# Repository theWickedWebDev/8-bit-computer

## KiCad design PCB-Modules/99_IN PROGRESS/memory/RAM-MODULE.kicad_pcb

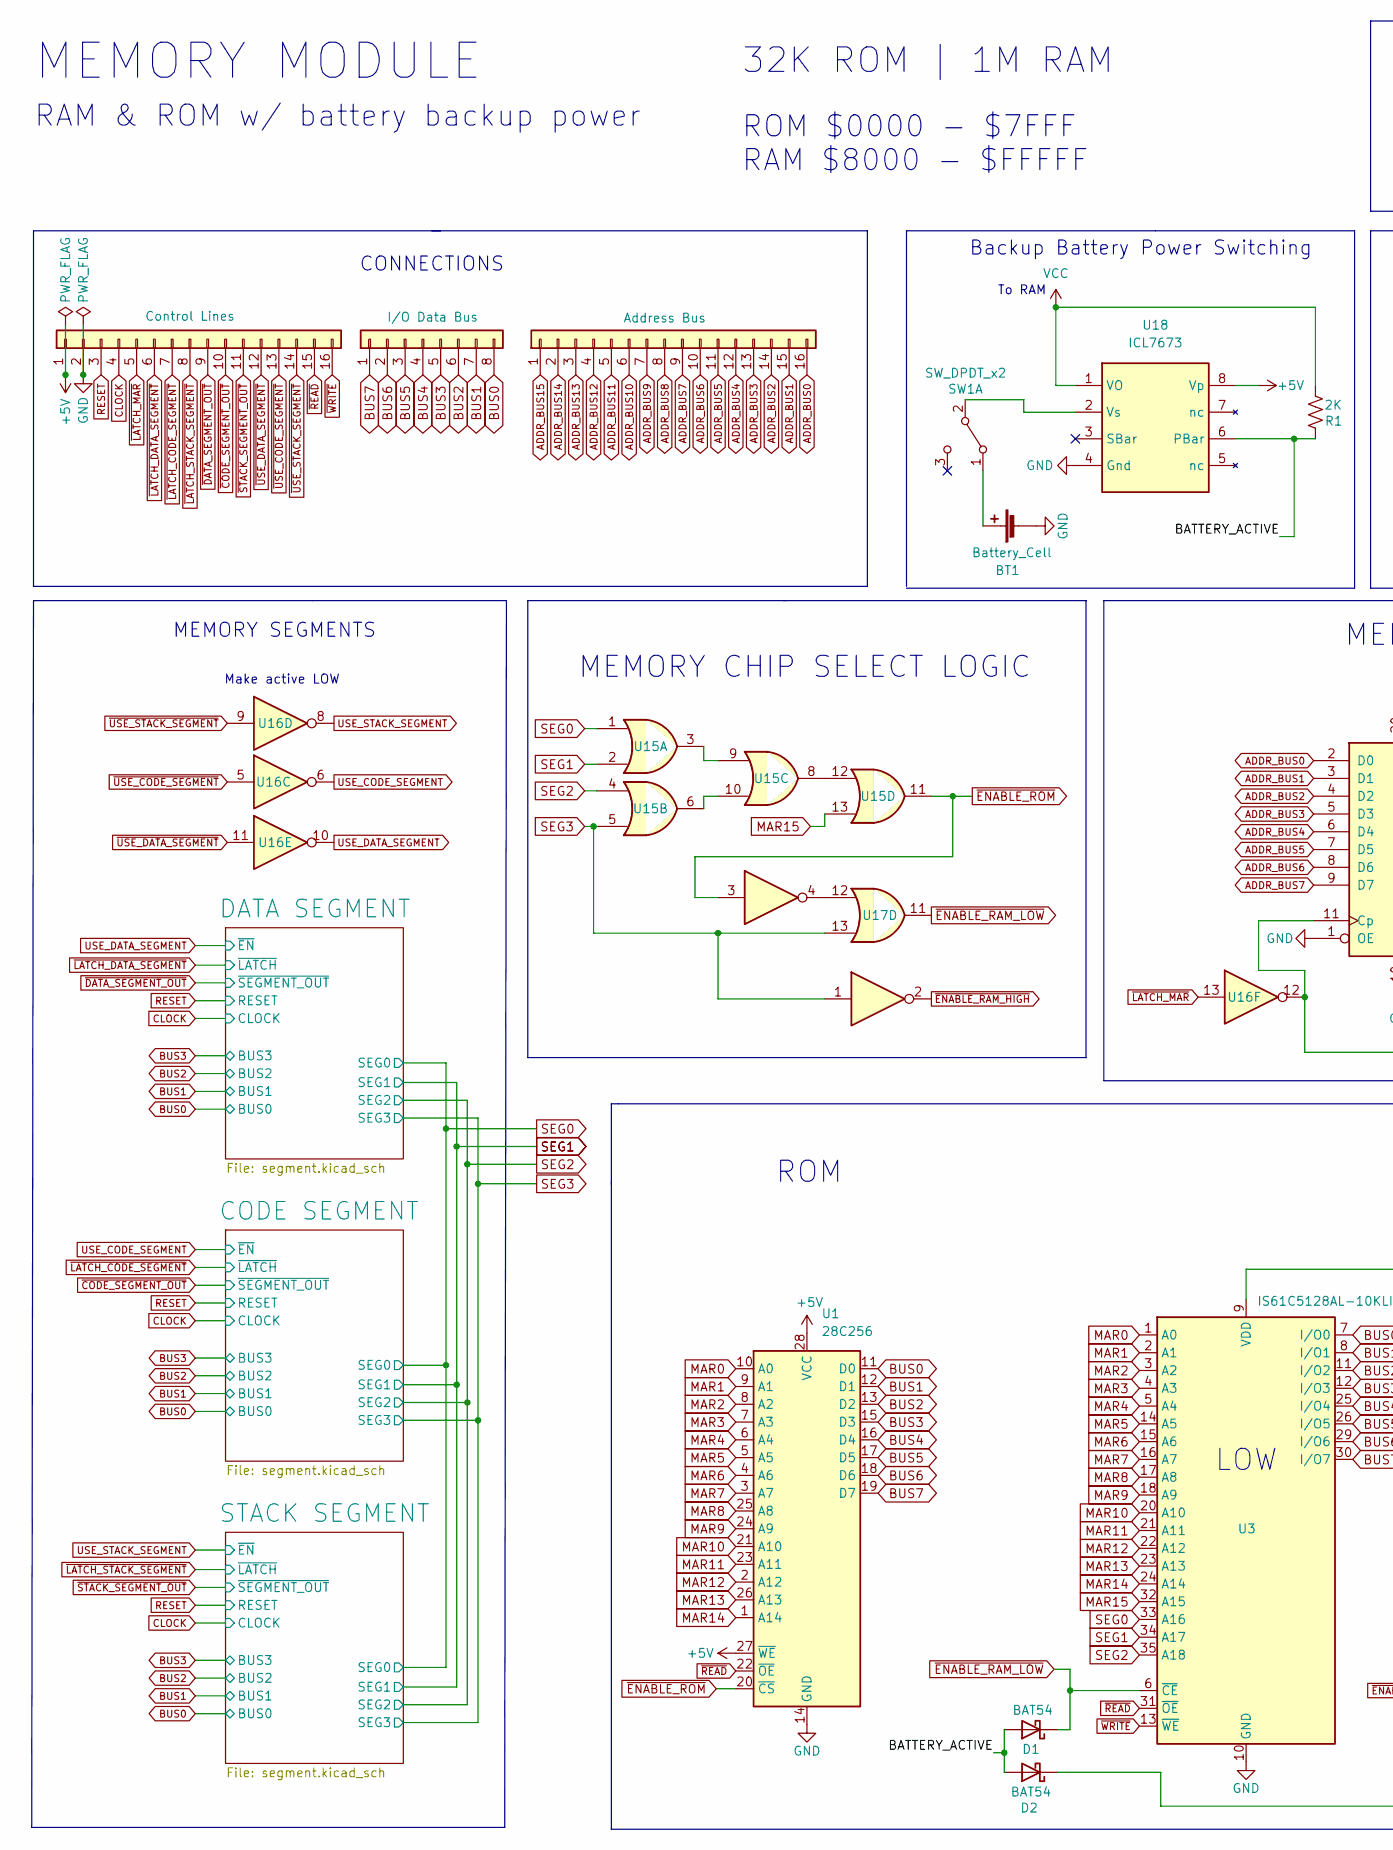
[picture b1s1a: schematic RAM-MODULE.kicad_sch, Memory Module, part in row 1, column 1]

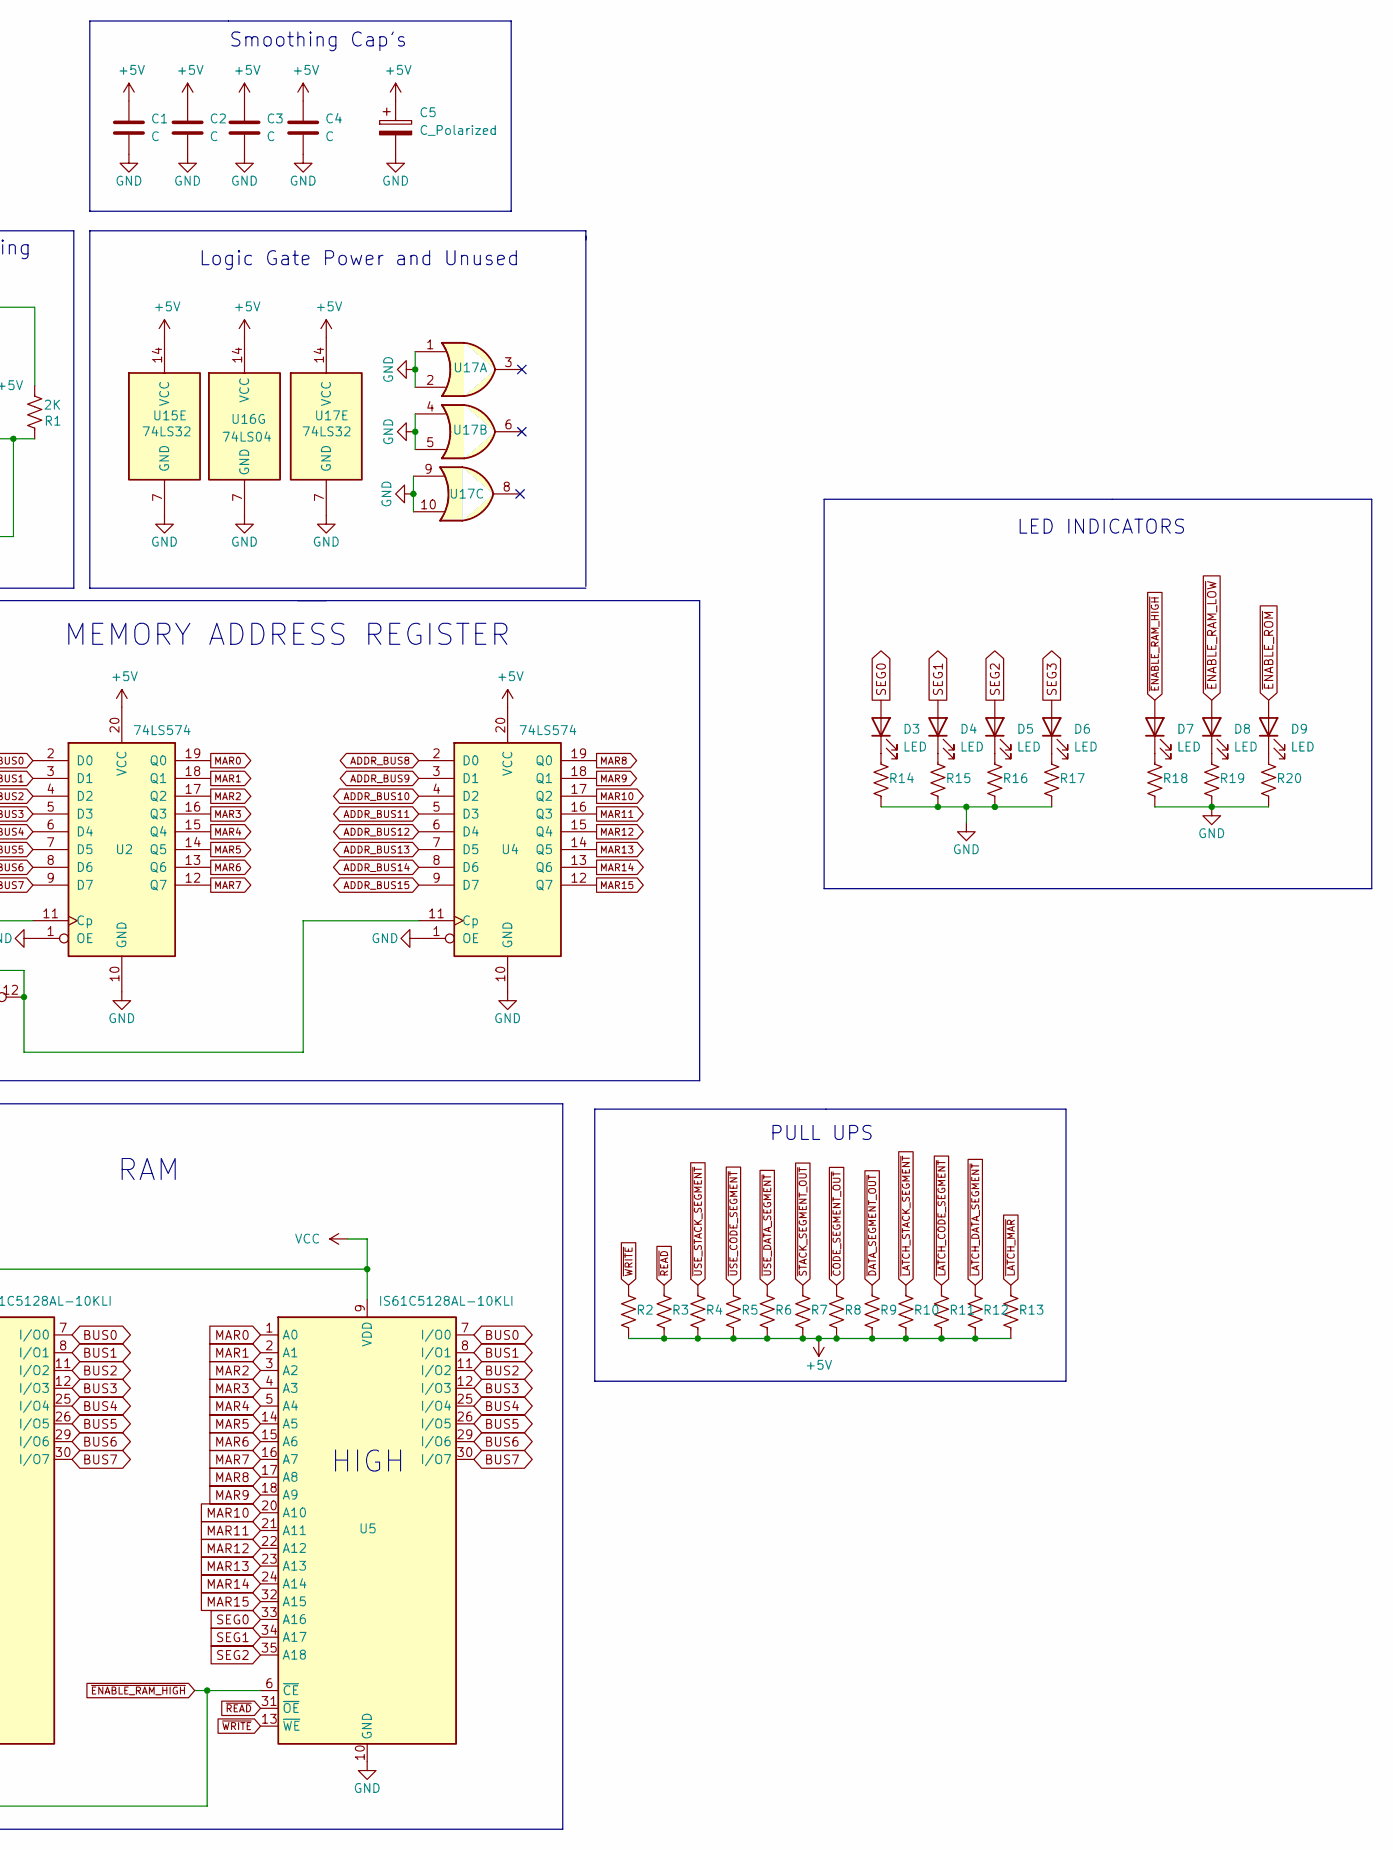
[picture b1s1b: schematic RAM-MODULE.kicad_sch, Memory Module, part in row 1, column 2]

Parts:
BT1: Battery_Cell; BatteryHolder_Keystone_106_1x20mm
C1, C2, C3, C4: C; C_0805_2012Metric
C5: C_Polarized; CP_Elec_4x3
D1, D2: BAT54; D_SOD-323F
D3, D4, D5, D6, D7, D8, D9: LED; LED_0805_2012Metric
J1, J3: Conn_01x16; PinHeader_1x16_P2.54mm_Vertical
J2: Conn_01x08; PinHeader_1x08_P2.54mm_Vertical
R1, R2, R3, R4, R5, R6, R7, R8, R9, R10, R11, R12, R13, R14, R15, R16, R17, R18, R19, R20: R_US; R_0805_2012Metric
SW1: SW_DPDT_x2; PinHeader_1x03_P2.54mm_Vertical
U1: 28C256; DIP_Socket-28_W11.9_W12.7_W15.24_W17.78_W18.5_3M_228-1277-0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
U2, U4: 74LS574; SOIC-20W_7.5x12.8mm_P1.27mm
U3, U5: IS61C5128AL-10KLI; SOJ-36_10.16x23.49mm_P1.27mm
U15, U17: 74LS32
U16: 74LS04
U18: ICL7673; DIP-8_W7.62mm

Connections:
+5V: C1.1, C2.1, C3.1, C4.1, C5.1, J3.1, R2.1, R3.1, R4.1, R5.1, R6.1, R7.1, R8.1, R9.1, R10.1, R11.1, R12.1, R13.1, U1.27 (~WE), U1.28 (VCC), U2.20 (VCC), U4.20 (VCC), U15.14 (VCC), U16.14 (VCC), U17.14 (VCC), U18.8 (Vp); also elsewhere on the board
/BATTERY_ACTIVE: D1.2 (A), D2.2 (A), R1.1, U18.6 (PBar)
ADDR_BUS0: J1.16, U2.2 (D0)
ADDR_BUS1: J1.15, U2.3 (D1)
ADDR_BUS2: J1.14, U2.4 (D2)
ADDR_BUS3: J1.13, U2.5 (D3)
ADDR_BUS4: J1.12, U2.6 (D4)
ADDR_BUS5: J1.11, U2.7 (D5)
ADDR_BUS6: J1.10, U2.8 (D6)
ADDR_BUS7: J1.9, U2.9 (D7)
ADDR_BUS8: J1.8, U4.2 (D0)
ADDR_BUS9: J1.7, U4.3 (D1)
ADDR_BUS10: J1.6, U4.4 (D2)
ADDR_BUS11: J1.5, U4.5 (D3)
ADDR_BUS12: J1.4, U4.6 (D4)
ADDR_BUS13: J1.3, U4.7 (D5)
ADDR_BUS14: J1.2, U4.8 (D6)
ADDR_BUS15: J1.1, U4.9 (D7)
BUS0: J2.8, U1.11 (D0), U3.7 (I/O0), U5.7 (I/O0); also elsewhere on the board
BUS1: J2.7, U1.12 (D1), U3.8 (I/O1), U5.8 (I/O1); also elsewhere on the board
BUS2: J2.6, U1.13 (D2), U3.11 (I/O2), U5.11 (I/O2); also elsewhere on the board
BUS3: J2.5, U1.15 (D3), U3.12 (I/O3), U5.12 (I/O3); also elsewhere on the board
BUS4: J2.4, U1.16 (D4), U3.25 (I/O4), U5.25 (I/O4)
BUS5: J2.3, U1.17 (D5), U3.26 (I/O5), U5.26 (I/O5)
BUS6: J2.2, U1.18 (D6), U3.29 (I/O6), U5.29 (I/O6)
BUS7: J2.1, U1.19 (D7), U3.30 (I/O7), U5.30 (I/O7)
CLOCK: J3.4; also elsewhere on the board
GND: BT1.2 (-), C1.2, C2.2, C3.2, C4.2, C5.2, J3.2, R14.1, R15.1, R16.1, R17.1, R18.1, R19.1, R20.1, U1.14 (GND), U2.1 (OE), U2.10 (GND), U3.10 (GND), U3.28 (GND), U4.1 (OE), U4.10 (GND), U5.10 (GND), U5.28 (GND), U15.7 (GND), U16.7 (GND), U17.1, U17.2, U17.4, U17.5, U17.7 (GND), U17.9, U17.10, U18.4 (Gnd); also elsewhere on the board
MAR0: U1.10 (A0), U2.19 (Q0), U3.1 (A0), U5.1 (A0)
MAR1: U1.9 (A1), U2.18 (Q1), U3.2 (A1), U5.2 (A1)
MAR2: U1.8 (A2), U2.17 (Q2), U3.3 (A2), U5.3 (A2)
MAR3: U1.7 (A3), U2.16 (Q3), U3.4 (A3), U5.4 (A3)
MAR4: U1.6 (A4), U2.15 (Q4), U3.5 (A4), U5.5 (A4)
MAR5: U1.5 (A5), U2.14 (Q5), U3.14 (A5), U5.14 (A5)
MAR6: U1.4 (A6), U2.13 (Q6), U3.15 (A6), U5.15 (A6)
MAR7: U1.3 (A7), U2.12 (Q7), U3.16 (A7), U5.16 (A7)
MAR8: U1.25 (A8), U3.17 (A8), U4.19 (Q0), U5.17 (A8)
MAR9: U1.24 (A9), U3.18 (A9), U4.18 (Q1), U5.18 (A9)
MAR10: U1.21 (A10), U3.20 (A10), U4.17 (Q2), U5.20 (A10)
MAR11: U1.23 (A11), U3.21 (A11), U4.16 (Q3), U5.21 (A11)
MAR12: U1.2 (A12), U3.22 (A12), U4.15 (Q4), U5.22 (A12)
MAR13: U1.26 (A13), U3.23 (A13), U4.14 (Q5), U5.23 (A13)
MAR14: U1.1 (A14), U3.24 (A14), U4.13 (Q6), U5.24 (A14)
MAR15: U3.32 (A15), U4.12 (Q7), U5.32 (A15), U15.13
unnamed: BT1.1 (+), SW1.1 (A)
unnamed: D3.1 (K), R14.2
unnamed: D4.1 (K), R15.2
unnamed: D5.1 (K), R16.2
unnamed: D6.1 (K), R17.2
unnamed: D7.1 (K), R18.2
unnamed: D8.1 (K), R19.2
unnamed: D9.1 (K), R20.2
unnamed: SW1.2 (B), U18.2 (Vs)
unnamed: U15.3, U15.9
unnamed: U15.6, U15.10
unnamed: U15.8, U15.12
unnamed: U16.4, U17.12
unnamed: U2.11 (Cp), U4.11 (Cp), U16.12
RESET: J3.3; also elsewhere on the board
SEG0: D3.2 (A), U3.33 (A16), U5.33 (A16), U15.1; also elsewhere on the board
SEG1: D4.2 (A), U3.34 (A17), U5.34 (A17), U15.2; also elsewhere on the board
SEG2: D5.2 (A), U3.35 (A18), U5.35 (A18), U15.4; also elsewhere on the board
SEG3: D6.2 (A), U15.5, U16.1, U17.13; also elsewhere on the board
USE_CODE_SEGMENT: U16.6; also elsewhere on the board
USE_DATA_SEGMENT: U16.10; also elsewhere on the board
USE_STACK_SEGMENT: U16.8; also elsewhere on the board
VCC: R1.2, U3.9 (VDD), U3.27 (VDD), U5.9 (VDD), U5.27 (VDD), U18.1 (VO)
~CODE_SEGMENT_OUT: J3.10, R8.2; also elsewhere on the board
~DATA_SEGMENT_OUT: J3.9, R9.2; also elsewhere on the board
~ENABLE_RAM_HIGH: D2.1 (K), D7.2 (A), U5.6 (~CE), U16.2
~ENABLE_RAM_LOW: D1.1 (K), D8.2 (A), U3.6 (~CE), U17.11
~ENABLE_ROM: D9.2 (A), U1.20 (~CS), U15.11, U16.3
~LATCH_CODE_SEGMENT: J3.7, R11.2; also elsewhere on the board
~LATCH_DATA_SEGMENT: J3.6, R12.2; also elsewhere on the board
~LATCH_MAR: J3.5, R13.2, U16.13
~LATCH_STACK_SEGMENT: J3.8, R10.2; also elsewhere on the board
~READ: J3.15, R3.2, U1.22 (~OE), U3.31 (~OE), U5.31 (~OE)
~STACK_SEGMENT_OUT: J3.11, R7.2; also elsewhere on the board
~USE_CODE_SEGMENT: J3.13, R5.2, U16.5
~USE_DATA_SEGMENT: J3.12, R6.2, U16.11
~USE_STACK_SEGMENT: J3.14, R4.2, U16.9
~WRITE: J3.16, R2.2, U3.13 (~WE), U5.13 (~WE)

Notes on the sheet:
MEMORY CHIP SELECT LOGIC
Logic Gate Power and Unused
HIGH
LED INDICATORS
MEMORY SEGMENTS
CONNECTIONS
MEMORY ADDRESS REGISTER
RAM & ROM w/ battery backup power
MEMORY MODULE
Make active LOW
ROM $0000 - $7FFF RAM $8000 - $FFFFF
To RAM
32K ROM | 1M RAM
PULL UPS
LOW
Smoothing Cap's
Backup Battery Power Switching
ROM
RAM

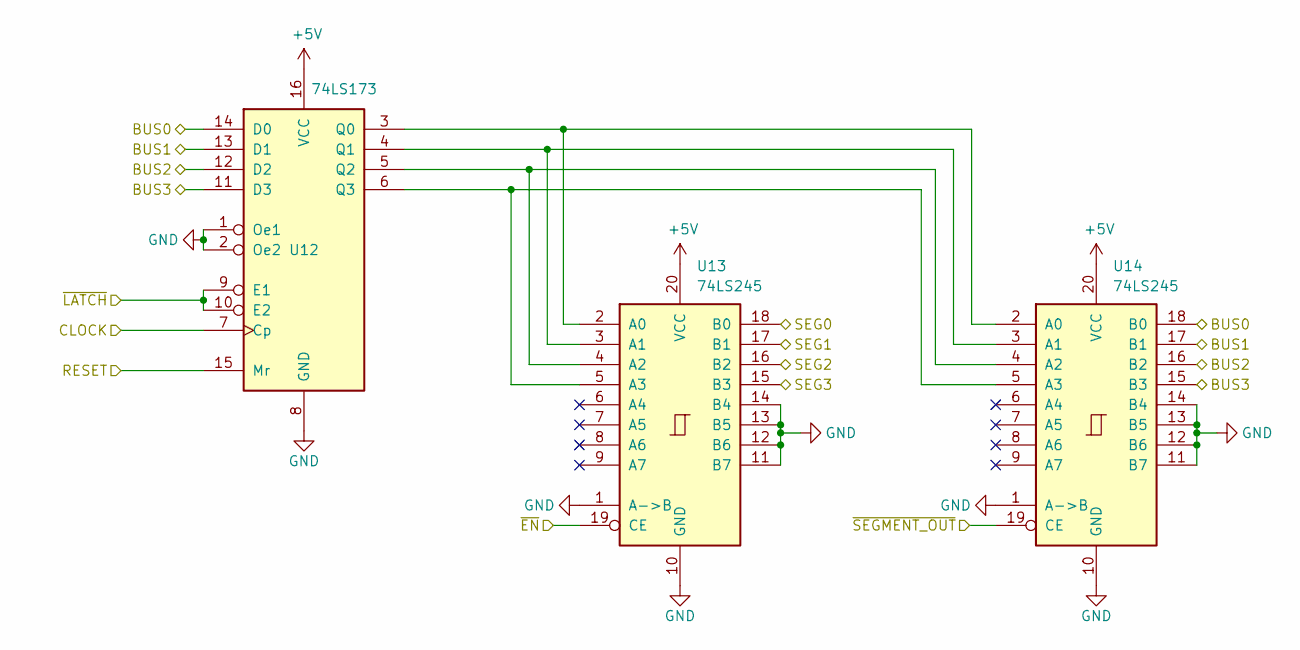
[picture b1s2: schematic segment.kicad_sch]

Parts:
U12: 74LS173; TSSOP-16_4.4x5mm_P0.65mm
U13, U14: 74LS245; TSSOP-20_4.4x6.5mm_P0.65mm

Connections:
+5V: U12.16 (VCC), U13.20 (VCC), U14.20 (VCC); also elsewhere on the board
BUS0: U12.14 (D0), U14.18 (B0); also elsewhere on the board
BUS1: U12.13 (D1), U14.17 (B1); also elsewhere on the board
BUS2: U12.12 (D2), U14.16 (B2); also elsewhere on the board
BUS3: U12.11 (D3), U14.15 (B3); also elsewhere on the board
CLOCK: U12.7 (Cp); also elsewhere on the board
GND: U12.1 (Oe1), U12.2 (Oe2), U12.8 (GND), U13.1 (A->B), U13.10 (GND), U13.11 (B7), U13.12 (B6), U13.13 (B5), U13.14 (B4), U14.1 (A->B), U14.10 (GND), U14.11 (B7), U14.12 (B6), U14.13 (B5), U14.14 (B4); also elsewhere on the board
unnamed: U12.3 (Q0), U13.2 (A0), U14.2 (A0)
unnamed: U12.4 (Q1), U13.3 (A1), U14.3 (A1)
unnamed: U12.5 (Q2), U13.4 (A2), U14.4 (A2)
unnamed: U12.6 (Q3), U13.5 (A3), U14.5 (A3)
RESET: U12.15 (Mr); also elsewhere on the board
SEG0: U13.18 (B0); also elsewhere on the board
SEG1: U13.17 (B1); also elsewhere on the board
SEG2: U13.16 (B2); also elsewhere on the board
SEG3: U13.15 (B3); also elsewhere on the board
USE_STACK_SEGMENT: U13.19 (CE); also elsewhere on the board
~LATCH_STACK_SEGMENT: U12.9 (E1), U12.10 (E2); also elsewhere on the board
~STACK_SEGMENT_OUT: U14.19 (CE); also elsewhere on the board

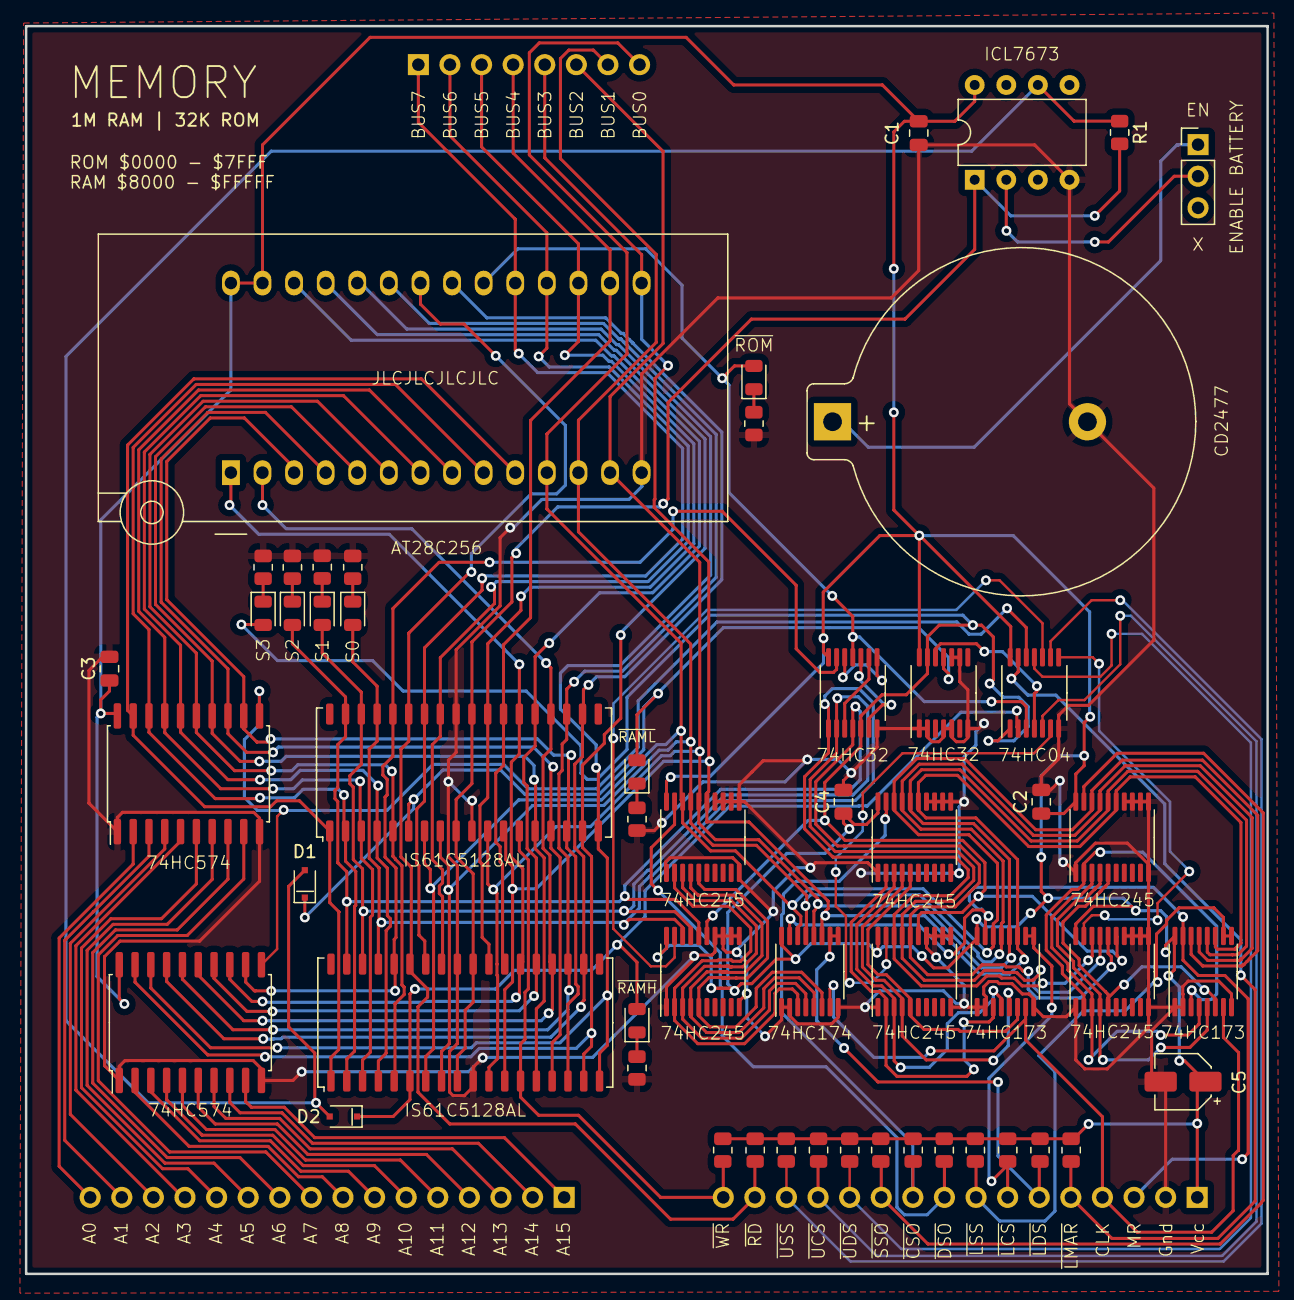
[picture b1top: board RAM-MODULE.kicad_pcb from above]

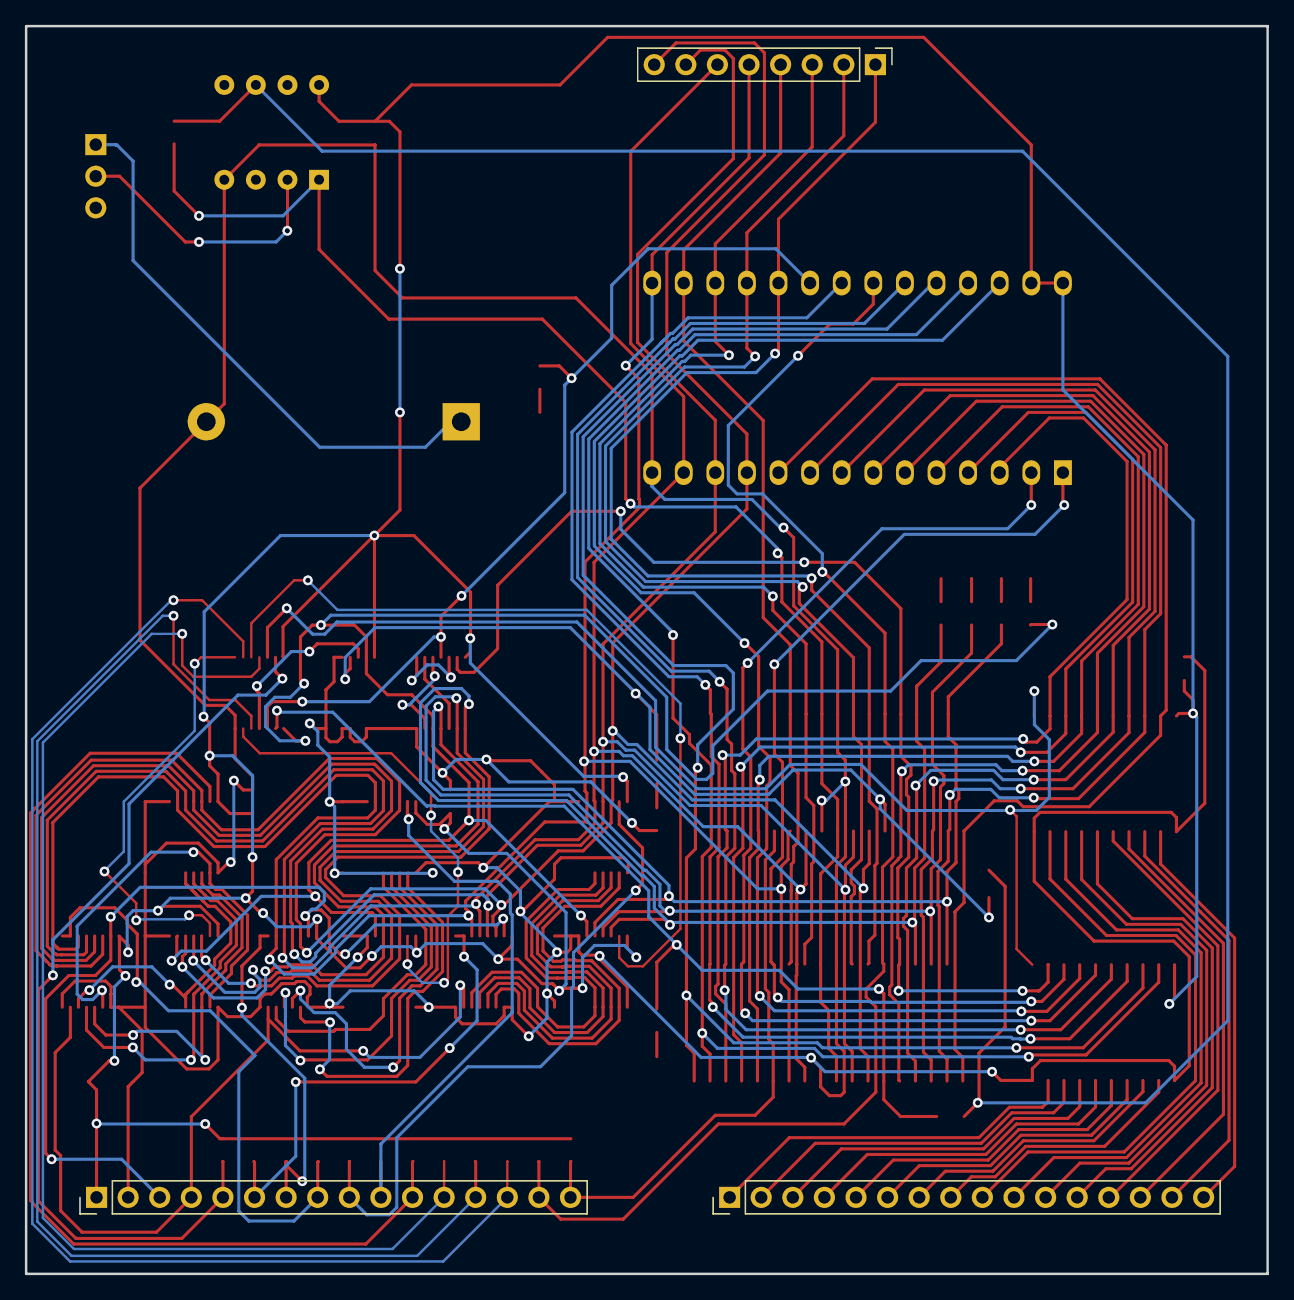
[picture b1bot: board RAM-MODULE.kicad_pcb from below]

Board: 4 copper layers, 99.8 x 100.3 mm, 57 parts (3 on the bottom side), 94 nets.

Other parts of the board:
U6, U9: 74LS173; TSSOP-16_4.4x5mm_P0.65mm
U7, U8, U10, U11: 74LS245; TSSOP-20_4.4x6.5mm_P0.65mm

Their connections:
+5V: U6.16 (VCC), U7.20 (VCC), U8.20 (VCC), U9.16 (VCC), U10.20 (VCC), U11.20 (VCC); also elsewhere on the board
BUS0: U6.14 (D0), U8.18 (B0), U9.14 (D0), U11.18 (B0); also elsewhere on the board
BUS1: U6.13 (D1), U8.17 (B1), U9.13 (D1), U11.17 (B1); also elsewhere on the board
BUS2: U6.12 (D2), U8.16 (B2), U9.12 (D2), U11.16 (B2); also elsewhere on the board
BUS3: U6.11 (D3), U8.15 (B3), U9.11 (D3), U11.15 (B3); also elsewhere on the board
CLOCK: U6.7 (Cp), U9.7 (Cp); also elsewhere on the board
GND: U6.1 (Oe1), U6.2 (Oe2), U6.8 (GND), U7.1 (A->B), U7.10 (GND), U7.11 (B7), U7.12 (B6), U7.13 (B5), U7.14 (B4), U8.1 (A->B), U8.10 (GND), U8.11 (B7), U8.12 (B6), U8.13 (B5), U8.14 (B4), U9.1 (Oe1), U9.2 (Oe2), U9.8 (GND), U10.1 (A->B), U10.10 (GND), U10.11 (B7), U10.12 (B6), U10.13 (B5), U10.14 (B4), U11.1 (A->B), U11.10 (GND), U11.11 (B7), U11.12 (B6), U11.13 (B5), U11.14 (B4); also elsewhere on the board
unnamed: U6.3 (Q0), U7.2 (A0), U8.2 (A0)
unnamed: U6.4 (Q1), U7.3 (A1), U8.3 (A1)
unnamed: U6.5 (Q2), U7.4 (A2), U8.4 (A2)
unnamed: U6.6 (Q3), U7.5 (A3), U8.5 (A3)
unnamed: U9.3 (Q0), U10.2 (A0), U11.2 (A0)
unnamed: U9.4 (Q1), U10.3 (A1), U11.3 (A1)
unnamed: U9.5 (Q2), U10.4 (A2), U11.4 (A2)
unnamed: U9.6 (Q3), U10.5 (A3), U11.5 (A3)
RESET: U6.15 (Mr), U9.15 (Mr); also elsewhere on the board
SEG0: U7.18 (B0), U10.18 (B0); also elsewhere on the board
SEG1: U7.17 (B1), U10.17 (B1); also elsewhere on the board
SEG2: U7.16 (B2), U10.16 (B2); also elsewhere on the board
SEG3: U7.15 (B3), U10.15 (B3); also elsewhere on the board
USE_CODE_SEGMENT: U10.19 (CE); also elsewhere on the board
USE_DATA_SEGMENT: U7.19 (CE); also elsewhere on the board
~CODE_SEGMENT_OUT: U11.19 (CE); also elsewhere on the board
~DATA_SEGMENT_OUT: U8.19 (CE); also elsewhere on the board
~LATCH_CODE_SEGMENT: U9.9 (E1), U9.10 (E2); also elsewhere on the board
~LATCH_DATA_SEGMENT: U6.9 (E1), U6.10 (E2); also elsewhere on the board

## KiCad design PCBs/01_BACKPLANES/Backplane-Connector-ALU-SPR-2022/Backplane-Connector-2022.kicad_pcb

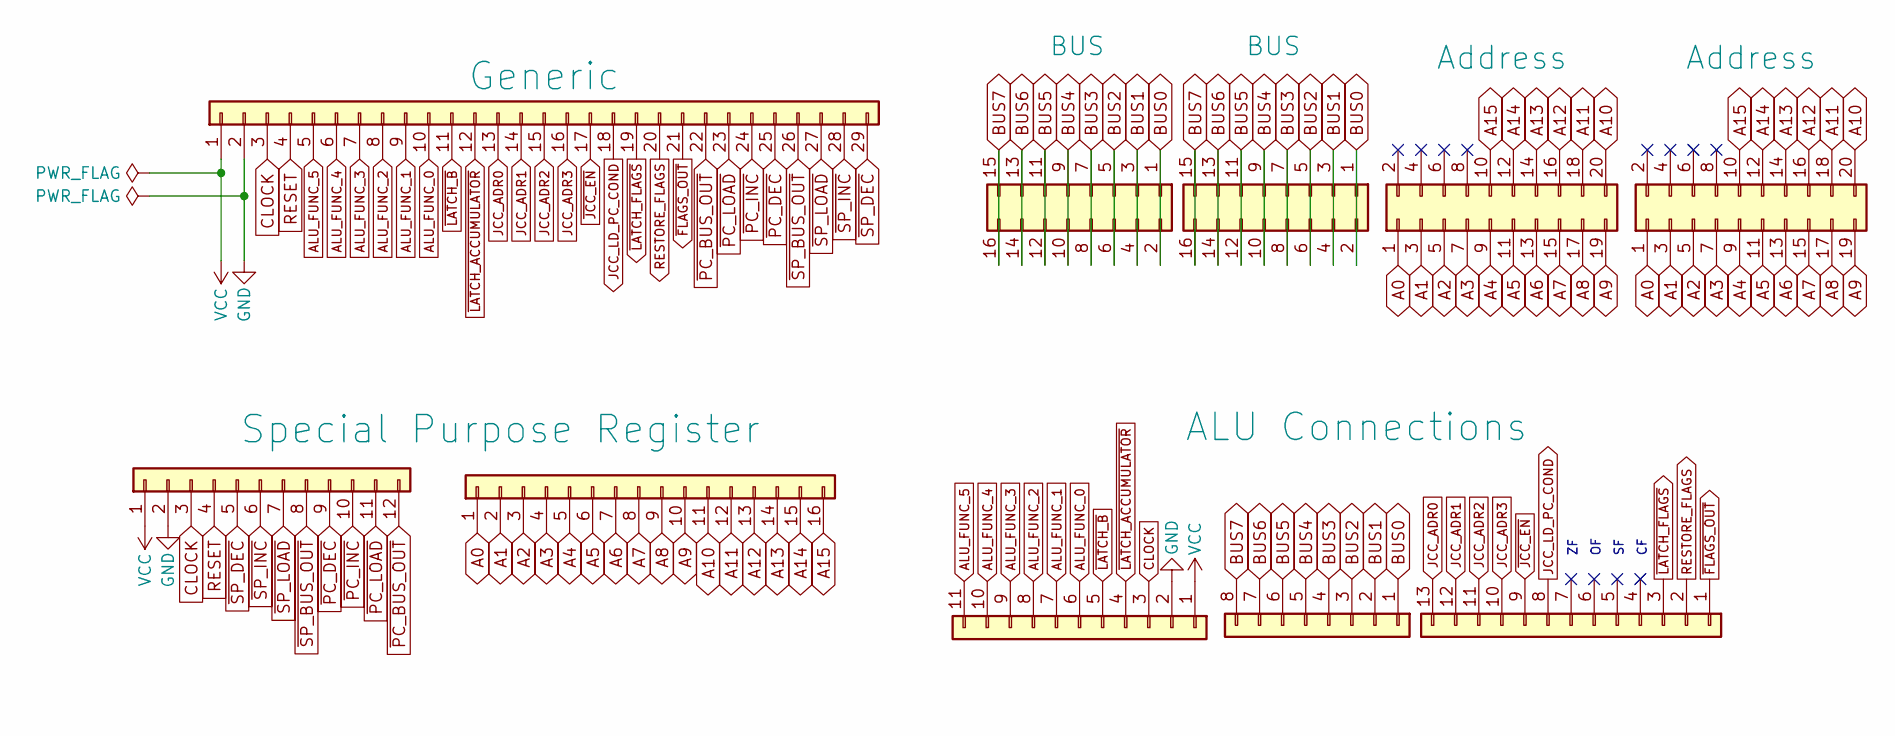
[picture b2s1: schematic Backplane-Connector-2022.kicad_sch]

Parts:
J1: Conn_01x12; PinSocket_1x12_P2.54mm_Horizontal
J2: Conn_01x29; PinSocket_1x29_P2.54mm_Horizontal
J3: Conn_01x16; PinSocket_1x16_P2.54mm_Horizontal
J4: Conn_01x12; PinSocket_1x11_P2.54mm_Horizontal
J5, J6: Conn_01x08; PinHeader_2x08_P2.54mm_Vertical
J7: Conn_01x08; PinSocket_1x08_P2.54mm_Horizontal
J8, J10: Conn_02x20_Odd_Even; IDC-Header_2x10_P2.54mm_Vertical
J9: Conn_01x13; PinSocket_1x13_P2.54mm_Horizontal

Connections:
A0: J3.1, J8.1, J10.1
A1: J3.2, J8.3, J10.3
A2: J3.3, J8.5, J10.5
A3: J3.4, J8.7, J10.7
A4: J3.5, J8.9, J10.9
A5: J3.6, J8.11, J10.11
A6: J3.7, J8.13, J10.13
A7: J3.8, J8.15, J10.15
A8: J3.9, J8.17, J10.17
A9: J3.10, J8.19, J10.19
A10: J3.11, J8.20, J10.20
A11: J3.12, J8.18, J10.18
A12: J3.13, J8.16, J10.16
A13: J3.14, J8.14, J10.14
A14: J3.15, J8.12, J10.12
A15: J3.16, J8.10, J10.10
ALU_FUNC_0: J2.10, J4.6
ALU_FUNC_1: J2.9, J4.7
ALU_FUNC_2: J2.8, J4.8
ALU_FUNC_3: J2.7, J4.9
ALU_FUNC_4: J2.6, J4.10
ALU_FUNC_5: J2.5, J4.11
BUS0: J5.1, J5.2, J6.1, J6.2, J7.1
BUS1: J5.3, J5.4, J6.3, J6.4, J7.2
BUS2: J5.5, J5.6, J6.5, J6.6, J7.3
BUS3: J5.7, J5.8, J6.7, J6.8, J7.4
BUS4: J5.9, J5.10, J6.9, J6.10, J7.5
BUS5: J5.11, J5.12, J6.11, J6.12, J7.6
BUS6: J5.13, J5.14, J6.13, J6.14, J7.7
BUS7: J5.15, J5.16, J6.15, J6.16, J7.8
CLOCK: J1.3, J2.3, J4.3
GND: J1.2, J2.2, J4.2
JCC_ADR0: J2.13, J9.13
JCC_ADR1: J2.14, J9.12
JCC_ADR2: J2.15, J9.11
JCC_ADR3: J2.16, J9.10
JCC_LD_PC_COND: J2.18, J9.8
RESET: J1.4, J2.4
RESTORE_FLAGS: J2.20, J9.2
VCC: J1.1, J2.1, J4.1
~FLAGS_OUT: J2.21, J9.1
~JCC_EN: J2.17, J9.9
~LATCH_ACCUMULATOR: J2.12, J4.4
~LATCH_B: J2.11, J4.5
~LATCH_FLAGS: J2.19, J9.3
~PC_BUS_OUT: J1.12, J2.22
~PC_DEC: J1.9, J2.25
~PC_INC: J1.10, J2.24
~PC_LOAD: J1.11, J2.23
~SP_BUS_OUT: J1.8, J2.26
~SP_DEC: J1.5, J2.29
~SP_INC: J1.6, J2.28
~SP_LOAD: J1.7, J2.27

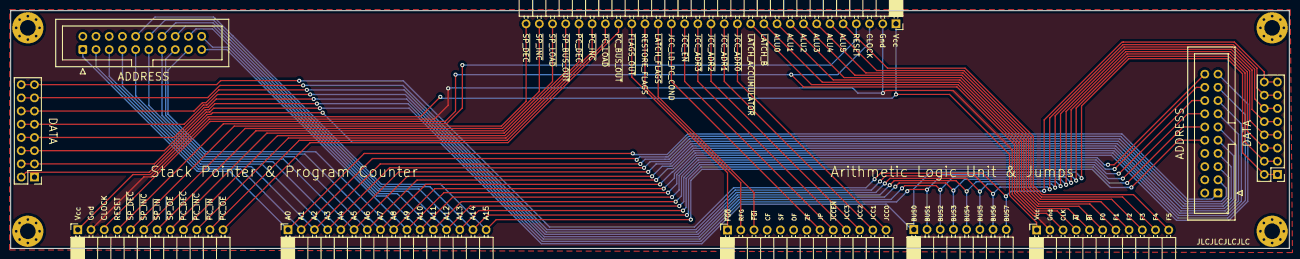
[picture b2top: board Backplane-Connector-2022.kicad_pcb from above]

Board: 2 copper layers, 245.9 x 45.7 mm, 10 parts (0 on the bottom side), 53 nets.

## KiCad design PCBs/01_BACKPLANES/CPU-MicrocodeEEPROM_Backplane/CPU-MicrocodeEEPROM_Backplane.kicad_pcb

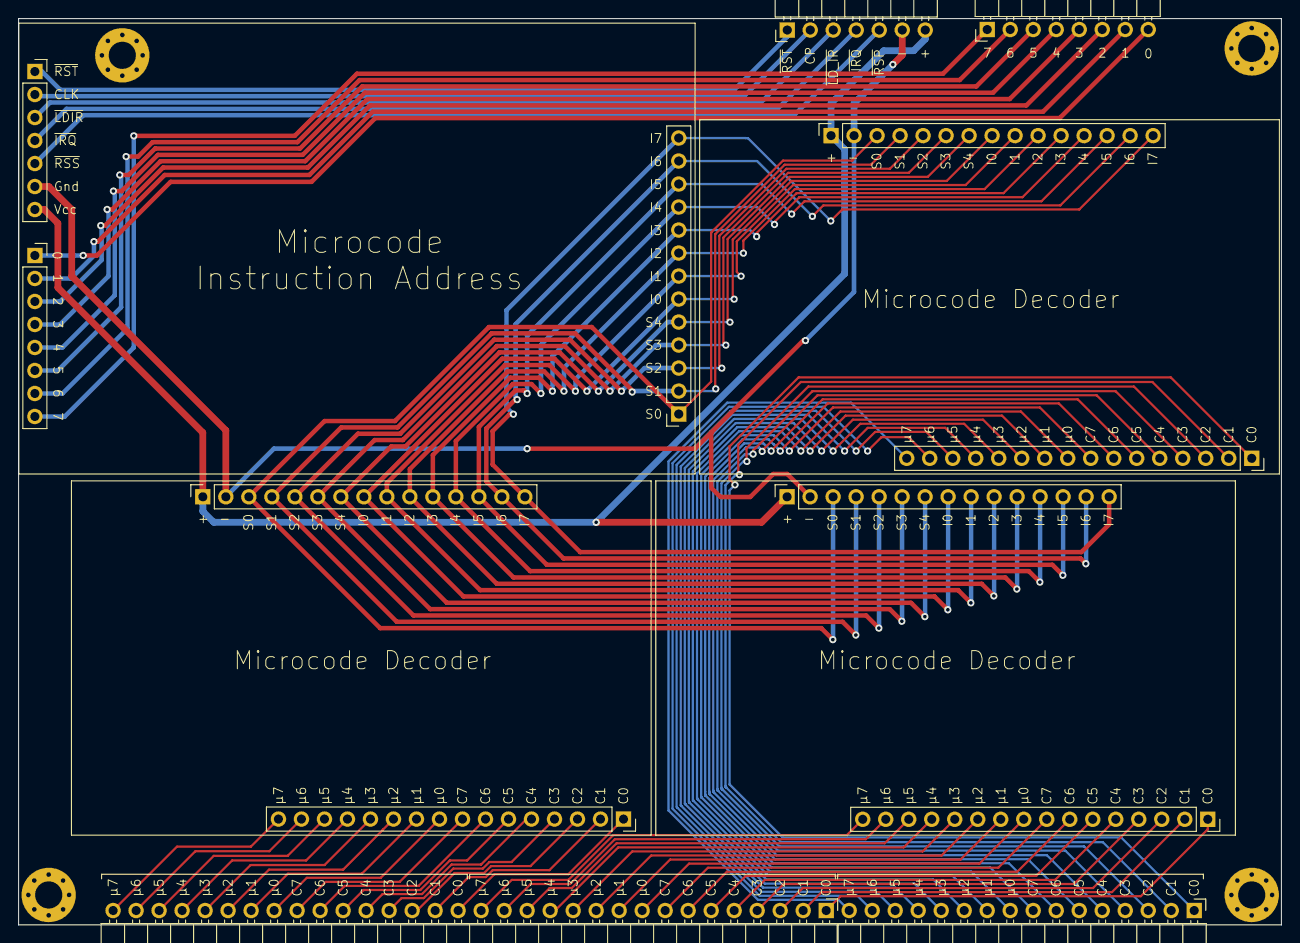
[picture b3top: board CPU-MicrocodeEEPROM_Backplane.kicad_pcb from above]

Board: 2 copper layers, 139.4 x 100.1 mm, 13 parts (0 on the bottom side), 76 nets.

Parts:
J1: Conn_01x08; PinSocket_1x08_P2.54mm_Vertical
J2: Conn_01x08; PinHeader_1x08_P2.54mm_Horizontal
J3: Conn_01x13; PinSocket_1x13_P2.54mm_Vertical
J4: Conn_01x07; PinHeader_1x07_P2.54mm_Horizontal
J5: Conn_01x07; PinSocket_1x07_P2.54mm_Vertical
J6, J9, J12: Conn_01x16; PinSocket_1x16_P2.54mm_Vertical
J7, J10, J13: Conn_01x15; PinSocket_1x15_P2.54mm_Vertical
J8: Conn_01x15; PinHeader_1x32_P2.54mm_Horizontal
J11: Conn_01x16; PinHeader_1x16_P2.54mm_Horizontal

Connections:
BUS0: J1.1, J2.8
BUS1: J1.2, J2.7
BUS2: J1.3, J2.6
BUS3: J1.4, J2.5
BUS4: J1.5, J2.4
BUS5: J1.6, J2.3
BUS6: J1.7, J2.2
BUS7: J1.8, J2.1
CLOCK: J4.2, J5.2
GND: J4.6, J5.6, J7.2, J10.2, J13.2
INSTRUCTION0: J3.6, J7.8, J10.8, J13.8
INSTRUCTION1: J3.7, J7.9, J10.9, J13.9
INSTRUCTION2: J3.8, J7.10, J10.10, J13.10
INSTRUCTION3: J3.9, J7.11, J10.11, J13.11
INSTRUCTION4: J3.10, J7.12, J10.12, J13.12
INSTRUCTION5: J3.11, J7.13, J10.13, J13.13
INSTRUCTION6: J3.12, J7.14, J10.14, J13.14
INSTRUCTION7: J3.13, J7.15, J10.15, J13.15
STEP0: J3.1, J7.3, J10.3, J13.3
STEP1: J3.2, J7.4, J10.4, J13.4
STEP2: J3.3, J7.5, J10.5, J13.5
STEP3: J3.4, J7.6, J10.6, J13.6
STEP4: J3.5, J7.7, J10.7, J13.7
VCC: J4.7, J5.7, J7.1, J10.1, J13.1
~DECODE_CONTROL_0b: J8.1, J9.1
~DECODE_CONTROL_0c: J11.1, J12.1
~DECODE_CONTROL_0: J6.1, J8.17
~DECODE_CONTROL_1b: J8.2, J9.2
~DECODE_CONTROL_1c: J11.2, J12.2
~DECODE_CONTROL_1: J6.2, J8.18
~DECODE_CONTROL_2b: J8.3, J9.3
~DECODE_CONTROL_2c: J11.3, J12.3
~DECODE_CONTROL_2: J6.3, J8.19
~DECODE_CONTROL_3b: J8.4, J9.4
~DECODE_CONTROL_3c: J11.4, J12.4
~DECODE_CONTROL_3: J6.4, J8.20
~DECODE_CONTROL_4b: J8.5, J9.5
~DECODE_CONTROL_4c: J11.5, J12.5
~DECODE_CONTROL_4: J6.5, J8.21
~DECODE_CONTROL_5b: J8.6, J9.6
~DECODE_CONTROL_5c: J11.6, J12.6
~DECODE_CONTROL_5: J6.6, J8.22
~DECODE_CONTROL_6b: J8.7, J9.7
~DECODE_CONTROL_6c: J11.7, J12.7
~DECODE_CONTROL_6: J6.7, J8.23
~DECODE_CONTROL_7b: J8.8, J9.8
~DECODE_CONTROL_7c: J11.8, J12.8
~DECODE_CONTROL_7: J6.8, J8.24
~INT_REQUEST: J4.4, J5.4
~LD_IR: J4.3, J5.3
~RESET_STEP: J4.5, J5.5
~RESET: J4.1, J5.1
μ0: J6.9, J8.25
μ0b: J8.9, J9.9
μ0c: J11.9, J12.9
μ1: J6.10, J8.26
μ1b: J8.10, J9.10
μ1c: J11.10, J12.10
μ2: J6.11, J8.27
μ2b: J8.11, J9.11
μ2c: J11.11, J12.11
μ3: J6.12, J8.28
μ3b: J8.12, J9.12
μ3c: J11.12, J12.12
μ4: J6.13, J8.29
μ4b: J8.13, J9.13
μ4c: J11.13, J12.13
μ5: J6.14, J8.30
μ5b: J8.14, J9.14
μ5c: J11.14, J12.14
μ6: J6.15, J8.31
μ6b: J8.15, J9.15
μ6c: J11.15, J12.15
μ7: J6.16, J8.32
μ7b: J8.16, J9.16
μ7c: J11.16, J12.16
